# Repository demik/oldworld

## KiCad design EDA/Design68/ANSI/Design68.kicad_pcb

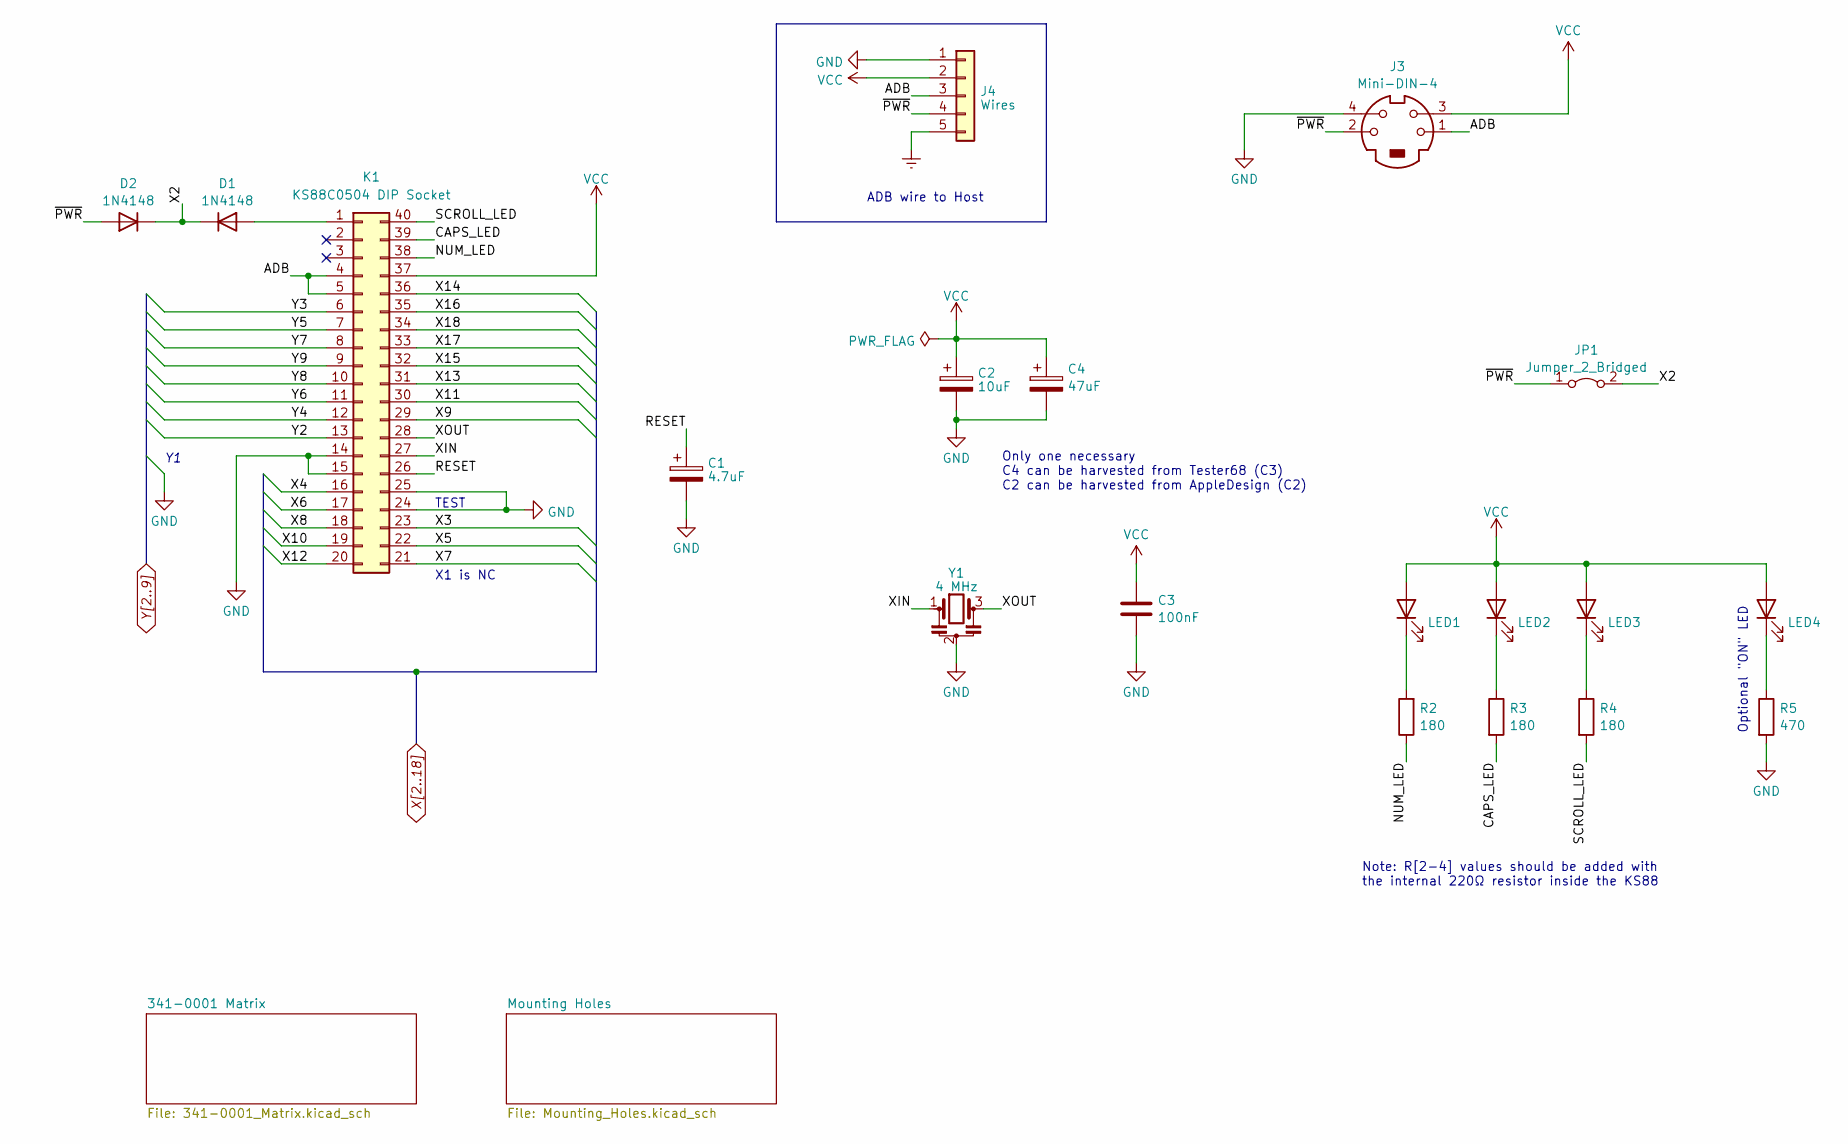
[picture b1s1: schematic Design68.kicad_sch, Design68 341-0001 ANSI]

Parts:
C1: 4.7uF; CP_Axial_L11.0mm_D5.0mm_P18.00mm_Horizontal
C2: 10uF; CP_Axial_L11.0mm_D5.0mm_P18.00mm_Horizontal
C3: 100nF; C_Axial_L3.8mm_D2.6mm_P10.00mm_Horizontal
C4: 47uF; C_0402_1005Metric_Pad0.74x0.62mm_HandSolder
D1, D2: 1N4148; D_DO-35_SOD27_P7.62mm_Horizontal
J3: Mini-DIN-4; 57491811
J4: Wires; PinHeader_1x05_P2.00mm_Horizontal
JP1: Jumper_2_Bridged; SolderJumper-2_P1.3mm_Bridged_Pad1.0x1.5mm
K1: KS88C0504 DIP Socket; DIP-40_W15.24mm_Socket
LED1, LED2, LED3, LED4: LED; LED_D3.0mm
R2, R3, R4: 180; R_Axial_DIN0207_L6.3mm_D2.5mm_P7.62mm_Horizontal
R5: 470; R_Axial_DIN0207_L6.3mm_D2.5mm_P7.62mm_Horizontal
Y1: 4 MHz; Resonator_Murata_CSTLSxxxG-3Pin_W8.0mm_H3.0mm

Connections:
/ADB: J3.1, J4.3, K1.4, K1.5
/CAPS_LED: K1.39, R3.2
/NUM_LED: K1.38, R2.1
/RESET: C1.1, K1.26
/SCROLL_LED: K1.40, R4.2
/XIN: K1.27, Y1.1
/XOUT: K1.28, Y1.3
/~PWR: D2.2 (A), J3.2, J4.4, JP1.1 (A)
Earth: J4.5
GND: C1.2, C2.2, C3.2, C4.2, J3.4, J4.1, K1.14, K1.15, K1.24, K1.25, R5.2, Y1.2; also elsewhere on the board
unnamed: D1.2 (A), K1.1
unnamed: LED1.1 (K), R2.2
unnamed: LED2.1 (K), R3.1
unnamed: LED3.1 (K), R4.1
unnamed: LED4.1 (K), R5.1
VCC: C2.1, C3.1, C4.1, J3.3, J4.2, K1.37, LED1.2 (A), LED2.2 (A), LED3.2 (A), LED4.2 (A)
X2: D1.1 (K), D2.1 (K), JP1.2 (B); also elsewhere on the board
X3: K1.23; also elsewhere on the board
X4: K1.16; also elsewhere on the board
X5: K1.22; also elsewhere on the board
X6: K1.17; also elsewhere on the board
X7: K1.21; also elsewhere on the board
X8: K1.18; also elsewhere on the board
X9: K1.29; also elsewhere on the board
X10: K1.19; also elsewhere on the board
X11: K1.30; also elsewhere on the board
X12: K1.20; also elsewhere on the board
X13: K1.31; also elsewhere on the board
X14: K1.36; also elsewhere on the board
X15: K1.32; also elsewhere on the board
X16: K1.35; also elsewhere on the board
X17: K1.33; also elsewhere on the board
X18: K1.34; also elsewhere on the board
Y2: K1.13; also elsewhere on the board
Y3: K1.6; also elsewhere on the board
Y4: K1.12; also elsewhere on the board
Y5: K1.7; also elsewhere on the board
Y6: K1.11; also elsewhere on the board
Y7: K1.8; also elsewhere on the board
Y8: K1.10; also elsewhere on the board
Y9: K1.9; also elsewhere on the board

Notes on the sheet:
TEST
Optional "ON" LED
ADB wire to Host
X1 is NC
Only one necessary C4 can be harvested from Tester68 (C3) C2 can be harvested from AppleDesign (C2)
Note: R[2-4] values should be added with the internal 220Ω resistor inside the KS88

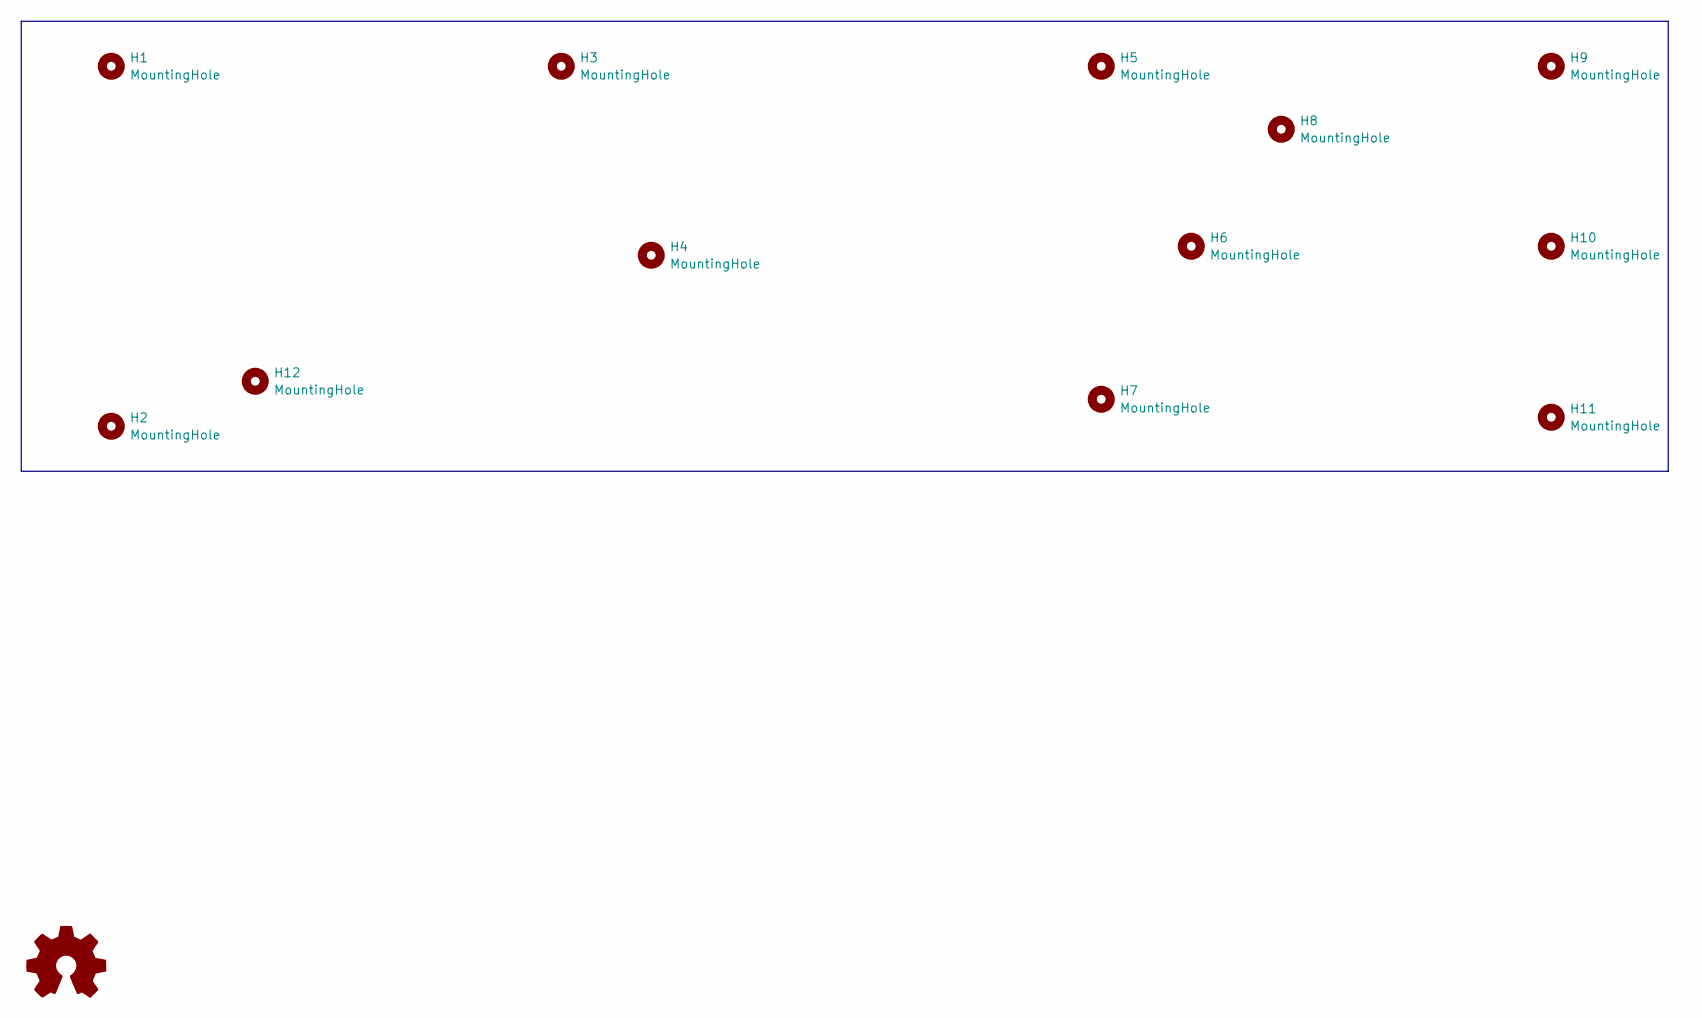
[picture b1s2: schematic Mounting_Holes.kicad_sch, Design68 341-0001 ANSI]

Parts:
H1, H2, H3, H4, H5, H6, H7, H8, H9, H10, H11, H12: MountingHole; MountingHole_5.5mm

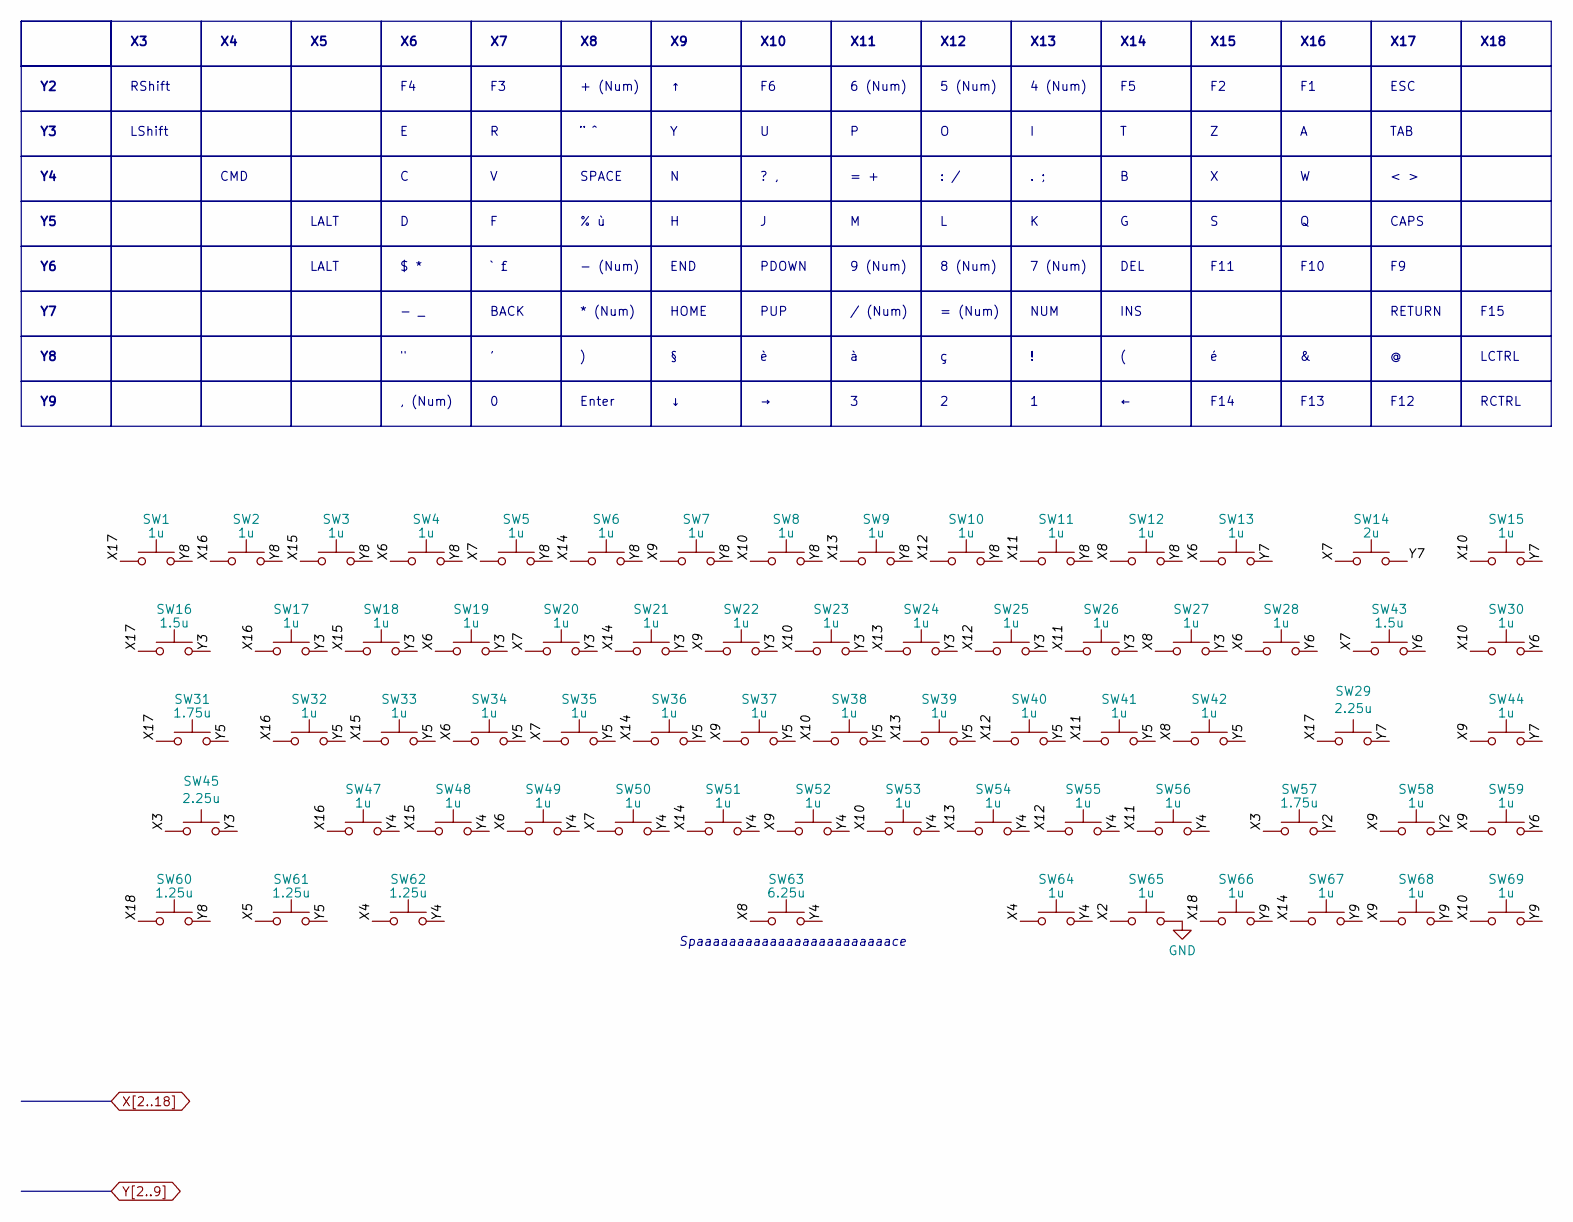
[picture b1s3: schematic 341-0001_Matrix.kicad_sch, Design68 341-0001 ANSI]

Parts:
SW1, SW2, SW3, SW4, SW5, SW6, SW7, SW8, SW9, SW10, SW11, SW12, SW13, SW15, SW17, SW18, SW19, SW20, SW21, SW22, SW23, SW24, SW25, SW26, SW27, SW28, SW30, SW32, SW33, SW34, SW35, SW36, SW37, SW38, SW39, SW40, SW41, SW42, SW44, SW47, SW48, SW49, SW50, SW51, SW52, SW53, SW54, SW55, SW56, SW58, SW59, SW64, SW65, SW66, SW67, SW68, SW69: 1u; SW_Cherry_MX_1.00u_PCB
SW14: 2u; SW_Cherry_MX_2.00u_PCB
SW16, SW43: 1.5u; SW_Cherry_MX_1.50u_PCB
SW29, SW45: 2.25u; SW_Cherry_MX_2.25u_PCB
SW31, SW57: 1.75u; SW_Cherry_MX_1.75u_PCB
SW60, SW61, SW62: 1.25u; SW_Cherry_MX_1.25u_PCB
SW63: 6.25u; SW_Cherry_MX_6.25u_PCB

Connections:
GND: SW65.2; also elsewhere on the board
X2: SW65.1; also elsewhere on the board
X3: SW45.1, SW57.1; also elsewhere on the board
X4: SW62.1, SW64.1; also elsewhere on the board
X5: SW61.1; also elsewhere on the board
X6: SW4.1, SW13.1, SW19.1, SW28.1, SW34.1, SW49.1; also elsewhere on the board
X7: SW5.1, SW14.1, SW20.1, SW35.1, SW43.1, SW50.1; also elsewhere on the board
X8: SW12.1, SW27.1, SW42.1, SW63.1; also elsewhere on the board
X9: SW7.1, SW22.1, SW37.1, SW44.1, SW52.1, SW58.1, SW59.1, SW68.1; also elsewhere on the board
X10: SW8.1, SW15.1, SW23.1, SW30.1, SW38.1, SW53.1, SW69.1; also elsewhere on the board
X11: SW11.1, SW26.1, SW41.1, SW56.1; also elsewhere on the board
X12: SW10.1, SW25.1, SW40.1, SW55.1; also elsewhere on the board
X13: SW9.1, SW24.1, SW39.1, SW54.1; also elsewhere on the board
X14: SW6.1, SW21.1, SW36.1, SW51.1, SW67.1; also elsewhere on the board
X15: SW3.1, SW18.1, SW33.1, SW48.1; also elsewhere on the board
X16: SW2.1, SW17.1, SW32.1, SW47.1; also elsewhere on the board
X17: SW1.1, SW16.1, SW29.1, SW31.1; also elsewhere on the board
X18: SW60.1, SW66.1; also elsewhere on the board
Y2: SW57.2, SW58.2; also elsewhere on the board
Y3: SW16.2, SW17.2, SW18.2, SW19.2, SW20.2, SW21.2, SW22.2, SW23.2, SW24.2, SW25.2, SW26.2, SW27.2, SW45.2; also elsewhere on the board
Y4: SW47.2, SW48.2, SW49.2, SW50.2, SW51.2, SW52.2, SW53.2, SW54.2, SW55.2, SW56.2, SW62.2, SW63.2, SW64.2; also elsewhere on the board
Y5: SW31.2, SW32.2, SW33.2, SW34.2, SW35.2, SW36.2, SW37.2, SW38.2, SW39.2, SW40.2, SW41.2, SW42.2, SW61.2; also elsewhere on the board
Y6: SW28.2, SW30.2, SW43.2, SW59.2; also elsewhere on the board
Y7: SW13.2, SW14.2, SW15.2, SW29.2, SW44.2; also elsewhere on the board
Y8: SW1.2, SW2.2, SW3.2, SW4.2, SW5.2, SW6.2, SW7.2, SW8.2, SW9.2, SW10.2, SW11.2, SW12.2, SW60.2; also elsewhere on the board
Y9: SW66.2, SW67.2, SW68.2, SW69.2; also elsewhere on the board

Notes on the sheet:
RETURN
% ù
ESC
RCTRL
+ (Num)
< >
X14
¨ ^
F11
5 (Num)
, (Num)
X16
: /
? ,
END
F10
- (Num)
8 (Num)
LALT
= (Num)
X17
. ;
Enter
X18
` £
NUM
CAPS
F12
RShift
X15
= +
F14
X13
TAB
INS
4 (Num)
X10
X12
$ *
* (Num)

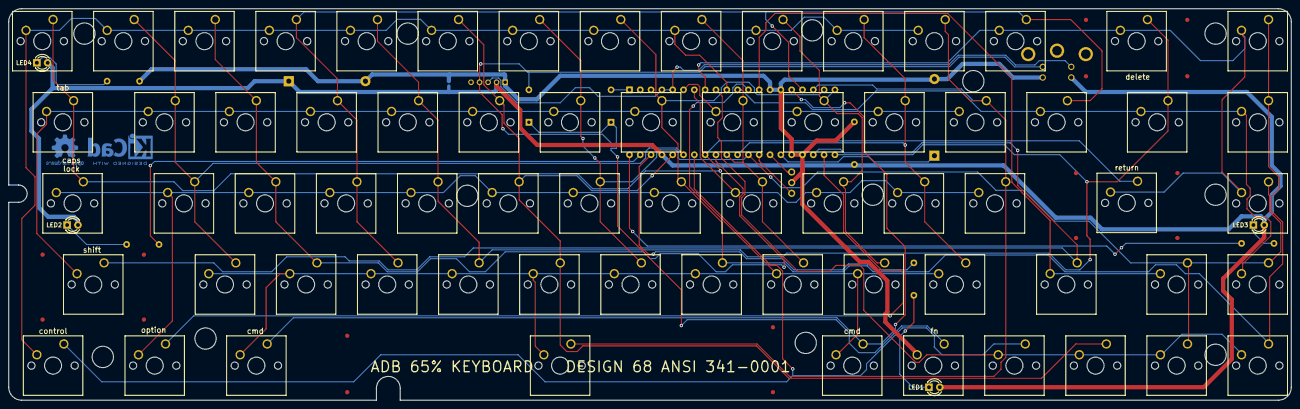
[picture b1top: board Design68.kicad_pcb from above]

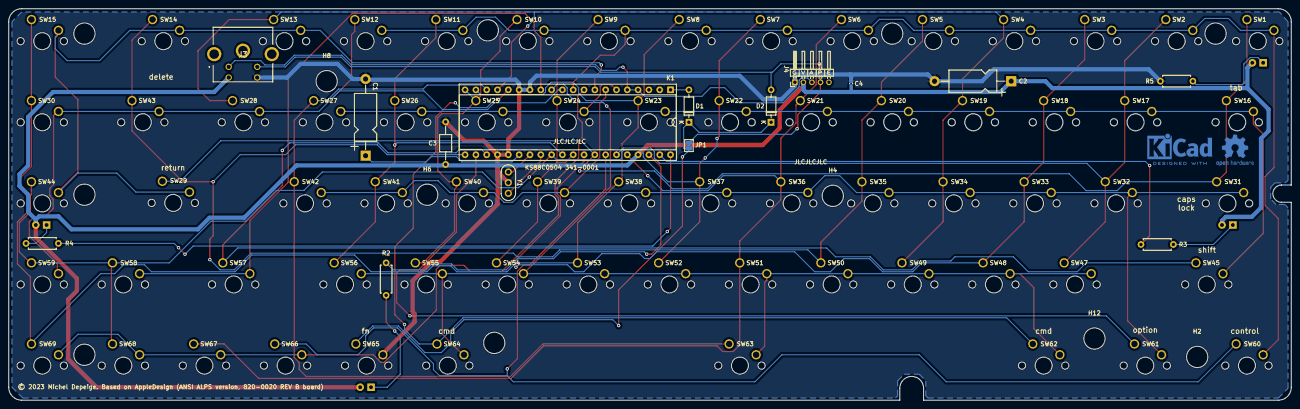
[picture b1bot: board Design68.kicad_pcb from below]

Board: 2 copper layers, 301.2 x 91.9 mm, 99 parts (27 on the bottom side), 40 nets.

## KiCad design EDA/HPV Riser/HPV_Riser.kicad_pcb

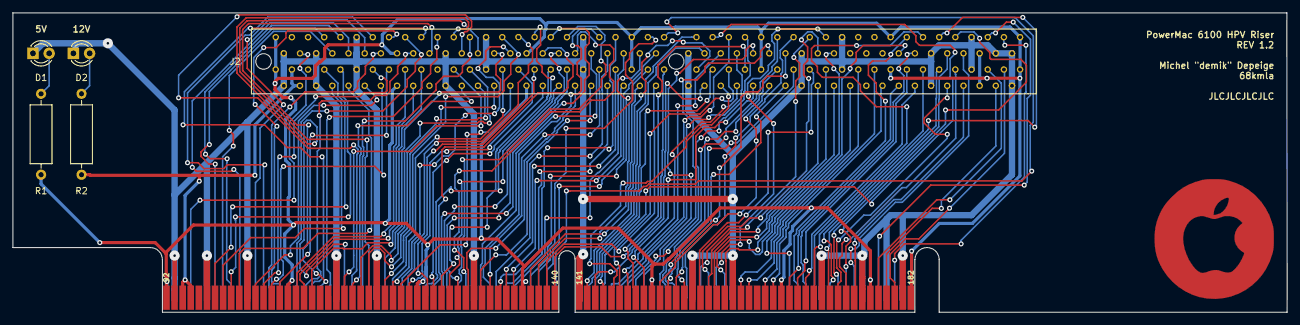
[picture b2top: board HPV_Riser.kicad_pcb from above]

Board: 2 copper layers, 200.0 x 47.0 mm, 6 parts (0 on the bottom side), 133 nets.

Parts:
D1: LED 5V; LED_D3.0mm
D2: LED 12V; LED_D3.0mm
J1: PowerMac_PDS
J2: PowerMac_PDS; EDAC_302-182-520-900
R1: 300; R_Axial_DIN0309_L9.0mm_D3.2mm_P12.70mm_Horizontal
R2: 1000; R_Axial_DIN0309_L9.0mm_D3.2mm_P12.70mm_Horizontal

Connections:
+5V: J1.1, J1.16, J1.32, J1.45, J1.59, J1.75, J1.86, J1.91, J1.92, J1.107, J1.123, J1.136, J1.150, J1.166, J1.177, J1.182, J2.1, J2.16, J2.32, J2.45, J2.59, J2.75, J2.86, J2.91, J2.92, J2.107, J2.123, J2.136, J2.150, J2.166, J2.177, J2.182, R1.2
+12V: J1.94, J1.95, J2.94, J2.95, R2.2
/A0: J1.126, J2.126
/A1: J1.35, J2.35
/A2: J1.127, J2.127
/A3: J1.36, J2.36
/A4: J1.128, J2.128
/A5: J1.37, J2.37
/A6: J1.129, J2.129
/A7: J1.38, J2.38
/A8: J1.131, J2.131
/A9: J1.40, J2.40
/A10: J1.132, J2.132
/A11: J1.41, J2.41
/A12: J1.133, J2.133
/A13: J1.42, J2.42
/A14: J1.134, J2.134
/A15: J1.43, J2.43
/A16: J1.135, J2.135
/A17: J1.44, J2.44
/A18: J1.137, J2.137
/A19: J1.46, J2.46
/A20: J1.138, J2.138
/A21: J1.47, J2.47
/A22: J1.139, J2.139
/A23: J1.48, J2.48
/A24: J1.140, J2.140
/A25: J1.49, J2.49
/A26: J1.142, J2.142
/A27: J1.51, J2.51
/A28: J1.143, J2.143
/A29: J1.52, J2.52
/A30: J1.144, J2.144
/A31: J1.53, J2.53
/ABB: J1.125, J2.125
/AddrAck: J1.124, J2.124
/AddrRtry: J1.18, J2.18
/Burst: J1.55, J2.55
/CPUint: J1.4, J2.4
/CacheIn: J1.54, J2.54
/D0: J1.98, J2.98
/D1: J1.99, J2.99
/D2: J1.100, J2.100
/D3: J1.101, J2.101
/D4: J1.103, J2.103
/D5: J1.104, J2.104
/D6: J1.105, J2.105
/D7: J1.106, J2.106
/D8: J1.114, J2.114
/D9: J1.115, J2.115
/D10: J1.116, J2.116
/D11: J1.117, J2.117
/D12: J1.119, J2.119
/D13: J1.120, J2.120
/D14: J1.121, J2.121
/D15: J1.122, J2.122
/D16: J1.151, J2.151
/D17: J1.152, J2.152
/D18: J1.153, J2.153
/D19: J1.154, J2.154
/D20: J1.156, J2.156
/D21: J1.157, J2.157
/D22: J1.158, J2.158
/D23: J1.159, J2.159
/D24: J1.167, J2.167
/D25: J1.168, J2.168
/D26: J1.169, J2.169
/D27: J1.170, J2.170
/D28: J1.172, J2.172
/D29: J1.173, J2.173
/D30: J1.174, J2.174
/D31: J1.175, J2.175
/D32: J1.7, J2.7
/D33: J1.8, J2.8
/D34: J1.9, J2.9
/D35: J1.10, J2.10
/D36: J1.12, J2.12
/D37: J1.13, J2.13
/D38: J1.14, J2.14
/D39: J1.15, J2.15
/D40: J1.23, J2.23
/D41: J1.24, J2.24
/D42: J1.25, J2.25
/D43: J1.26, J2.26
/D44: J1.28, J2.28
/D45: J1.29, J2.29
/D46: J1.30, J2.30
/D47: J1.31, J2.31
/D48: J1.60, J2.60
/D49: J1.61, J2.61
/D50: J1.62, J2.62
/D51: J1.63, J2.63
/D52: J1.65, J2.65
/D53: J1.66, J2.66
/D54: J1.67, J2.67
/D55: J1.68, J2.68
/D56: J1.76, J2.76
/D57: J1.77, J2.77
/D58: J1.78, J2.78
/D59: J1.79, J2.79
/D60: J1.81, J2.81
/D61: J1.82, J2.82
/D62: J1.83, J2.83
/D63: J1.84, J2.84
/DBB: J1.17, J2.17
/DataRtry: J1.19, J2.19
/Global: J1.58, J2.58
/I2C_clock: J1.164, J2.164
/I2C_data: J1.165, J2.165
/NuDump: J1.20, J2.20
/PDS_CLK: J1.89, J2.89
/PDS_IRQ2: J1.180, J2.180
/PDS_REQ: J1.178, J2.178
/PdsGrant: J1.179, J2.179
/Reset: J1.87, J2.87
/Rsrv: J1.56, J2.56
/Shared: J1.57, J2.57
/TC0: J1.161, J2.161
/TC1: J1.162, J2.162
/TS0: J1.108, J2.108
/TS1: J1.109, J2.109
/TS2: J1.110, J2.110
/TT0: J1.145, J2.145
/TT1: J1.146, J2.146
/TT2: J1.147, J2.147
/TT3: J1.148, J2.148
/TT4: J1.149, J2.149
/XferAck: J1.33, J2.33
/XferErrAck: J1.34, J2.34
/XferStart: J1.21, J2.21
GND: D1.1, D2.1, J1.2, J1.6, J1.11, J1.22, J1.27, J1.39, J1.50, J1.64, J1.69, J1.80, J1.85, J1.88, J1.90, J1.93, J1.97, J1.102, J1.113, J1.118, J1.130, J1.141, J1.155, J1.160, J1.171, J1.176, J1.181, J2.2, J2.6, J2.11, J2.22, J2.27, J2.39, J2.50, J2.64, J2.69, J2.80, J2.85, J2.88, J2.90, J2.93, J2.97, J2.102, J2.113, J2.118, J2.130, J2.141, J2.155, J2.160, J2.171, J2.176, J2.181
unnamed: D1.2, R1.1
unnamed: D2.2, R2.1

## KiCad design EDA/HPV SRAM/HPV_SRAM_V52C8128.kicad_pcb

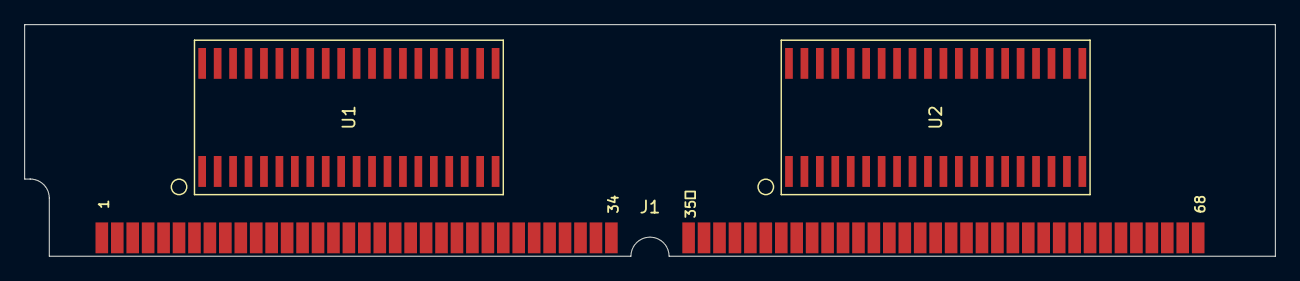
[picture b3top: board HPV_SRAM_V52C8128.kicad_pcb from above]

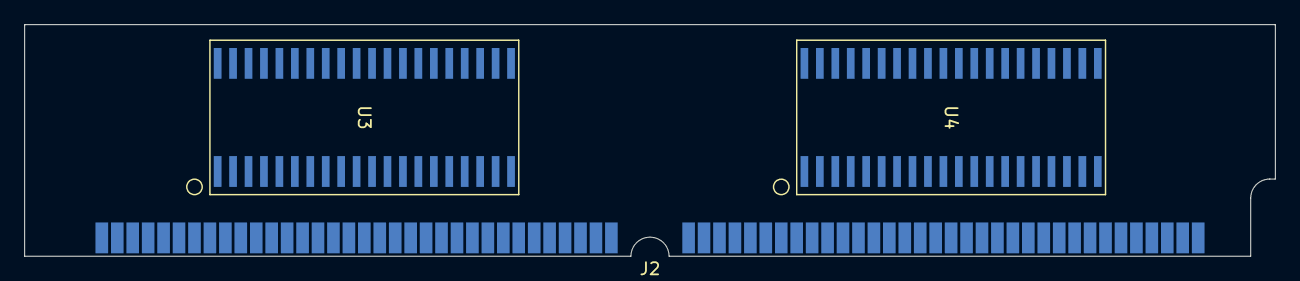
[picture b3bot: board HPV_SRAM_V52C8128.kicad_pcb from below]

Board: 2 copper layers, 102.9 x 19.1 mm, 6 parts (3 on the bottom side), 54 nets, no tracks yet.

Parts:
J1, J2: SIMM-68
U1, U2, U3, U4: V52C8128; SOJ-40

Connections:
+5V: J1.1, J1.29, J1.52, J2.1, J2.29, J2.52, U1.11, U1.20, U2.11, U2.20, U3.11, U3.20, U4.11, U4.20
/A0: J1.15, J2.15
/A1: J1.16, J2.16
/A2: J1.17, J2.17
/A3: J1.18, J2.18
/A4: J1.33, J2.33
/A5: J1.34, J2.34
/A6: J1.48, J2.48
/A7: J1.49, J2.49
/A8: J1.50, J2.50
/CAS0: J1.32, J2.32
/CAS1: J1.66, J2.66
/DQ0: J1.6, J2.6, U1.7
/DQ1: J1.7, J2.7, U1.8
/DQ2: J1.14, J2.14, U1.9
/DQ3: J1.13, J2.13, U1.10
/DQ4: J1.24, J2.24, U1.31
/DQ5: J1.25, J2.25, U1.32
/DQ6: J1.31, J2.31, U1.33
/DQ7: J1.30, J2.30, U1.34
/DQ8: J1.40, J2.40, U3.7
/DQ9: J1.41, J2.41, U3.8
/DQ11: J1.46, J2.46, U3.10
/DQ12: J1.58, J2.58, U3.31
/DQ13: J1.59, J2.59, U3.32
/DQ14: J1.65, J2.65, U3.33
/DQ15: J1.64, J2.64, U3.34
/DR-OE0: J1.5, J2.5, U1.6
/DSF: J1.2, J2.2, U1.29, U2.29, U3.29, U4.29
/DT-OE1: J1.39, J2.39
/RAS: J1.11, J2.11, U1.14, U3.14
/SC: J1.36, J2.36, U1.1, U2.1, U3.1, U4.1
/SDQ0: J1.3, J2.3, U1.2
/SDQ1: J1.4, J2.4, U1.3
/SDQ2: J1.9, J2.9, U1.4
/SDQ3: J1.8, J2.8, U1.5
/SDQ4: J1.21, J2.21, U1.36
/SDQ5: J1.22, J2.22, U1.37
/SDQ6: J1.27, J2.27, U1.38
/SDQ7: J1.26, J2.26, U1.39
/SDQ8: J1.37, J2.37, U3.2
/SDQ9: J1.38, J2.38, U3.3
/SDQ10: J1.43, J2.43, U3.4
/SDQ11: J1.42, J2.42, U3.5
/SDQ12: J1.55, J2.55, U3.36
/SDQ13: J1.56, J2.56, U3.37
/SDQ14: J1.61, J2.61, U3.38
/SDQ15: J1.60, J2.60, U3.39
/SE0: J1.12, J2.12
/SE1: J1.45, J2.45
/SQ10: J1.47, J2.47
/WE0: J1.10, J2.10, U1.12
/WE1: J1.44, J2.44
GND: J1.19, J1.20, J1.35, J1.53, J1.54, J1.67, J1.68, J2.19, J2.20, J2.35, J2.53, J2.54, J2.67, J2.68, U1.30, U1.40, U2.30, U2.40, U3.30, U3.40, U4.30, U4.40

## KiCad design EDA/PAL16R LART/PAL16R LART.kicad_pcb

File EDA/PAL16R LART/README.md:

# PAL16R LART

## Introduction

The PAL16R LART (for **L**ogic **A**nalyzing and **R**eversing **T**ool) is a small tool that can be used to help reversing PAL16s in live environement.

The small PCB can be fitted with a ZIF socket and additional pins for a logic analyzer. It's supposed to be installed in a socket on the original board.

## How to build

The Gerber files are avaiable in the release section here:
[https://github.com/demik/oldworld/releases/tag/PAL16R_LART%2Fv1.0.0](https://github.com/demik/oldworld/releases/tag/PAL16R_LART%2Fv1.0.0)

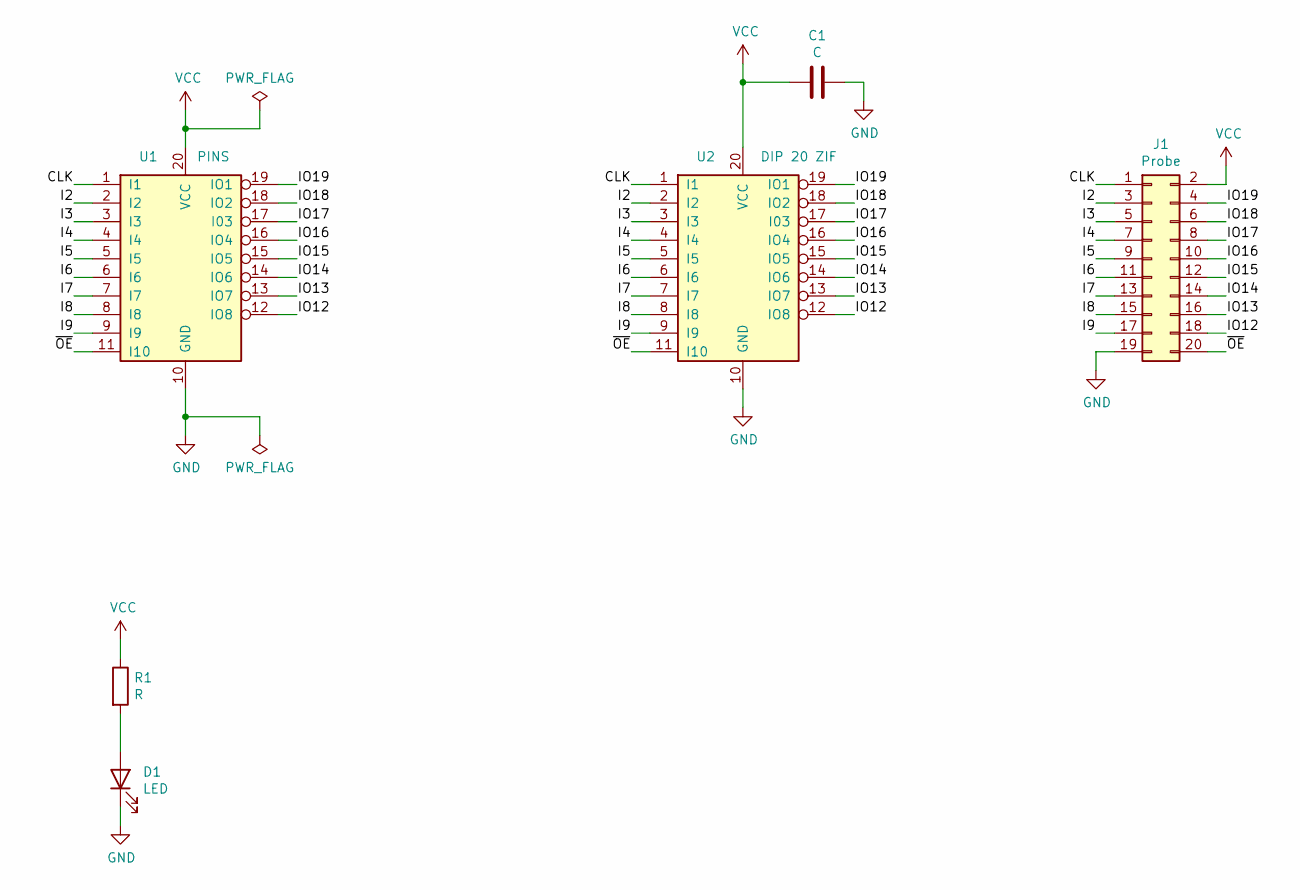
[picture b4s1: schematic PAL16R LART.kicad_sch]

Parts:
C1: C; C_Disc_D4.3mm_W1.9mm_P5.00mm
D1: LED; LED_D3.0mm
J1: Probe; PinHeader_2x10_P2.54mm_Vertical
R1: R; R_Axial_DIN0207_L6.3mm_D2.5mm_P7.62mm_Horizontal
U1: PINS; DIP-20_W7.62mm
U2: DIP 20 ZIF; DIP_Socket-20_W4.3_W5.08_W7.62_W10.16_W10.9_3M_220-3342-00-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

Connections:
/CLK: J1.1, U1.1 (I1), U2.1 (I1)
/I2: J1.3, U1.2 (I2), U2.2 (I2)
/I3: J1.5, U1.3 (I3), U2.3 (I3)
/I4: J1.7, U1.4 (I4), U2.4 (I4)
/I5: J1.9, U1.5 (I5), U2.5 (I5)
/I6: J1.11, U1.6 (I6), U2.6 (I6)
/I7: J1.13, U1.7 (I7), U2.7 (I7)
/I8: J1.15, U1.8 (I8), U2.8 (I8)
/I9: J1.17, U1.9 (I9), U2.9 (I9)
/IO12: J1.18, U1.12 (IO8), U2.12 (IO8)
/IO13: J1.16, U1.13 (IO7), U2.13 (IO7)
/IO14: J1.14, U1.14 (IO6), U2.14 (IO6)
/IO15: J1.12, U1.15 (IO5), U2.15 (IO5)
/IO16: J1.10, U1.16 (IO4), U2.16 (IO4)
/IO17: J1.8, U1.17 (I03), U2.17 (I03)
/IO18: J1.6, U1.18 (IO2), U2.18 (IO2)
/IO19: J1.4, U1.19 (IO1), U2.19 (IO1)
/~OE: J1.20, U1.11 (I10), U2.11 (I10)
GND: C1.1, D1.1 (K), J1.19, U1.10 (GND), U2.10 (GND)
unnamed: D1.2 (A), R1.2
VCC: C1.2, J1.2, R1.1, U1.20 (VCC), U2.20 (VCC)

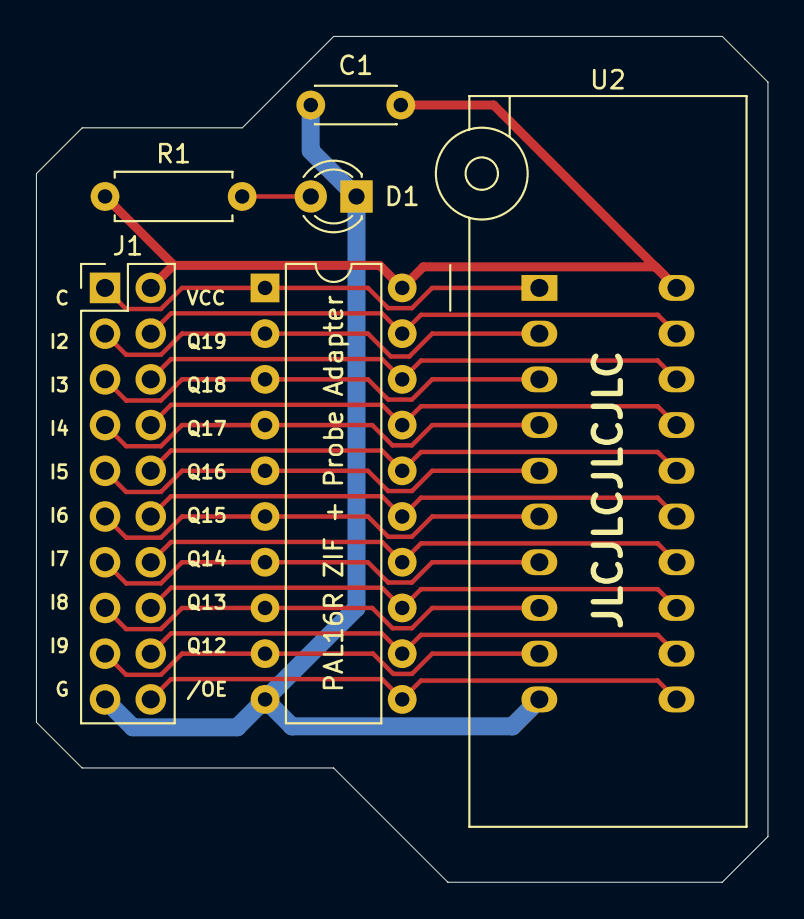
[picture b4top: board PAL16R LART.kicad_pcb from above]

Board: 2 copper layers, 40.6 x 47.0 mm, 6 parts (0 on the bottom side), 21 nets.

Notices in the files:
EDA/Design68/ANSI/Design68.kicad_pcb:
© 2023 Michel Depeige. Based on AppleDesign (ANSI ALPS version, 820-0020 REV B board)
